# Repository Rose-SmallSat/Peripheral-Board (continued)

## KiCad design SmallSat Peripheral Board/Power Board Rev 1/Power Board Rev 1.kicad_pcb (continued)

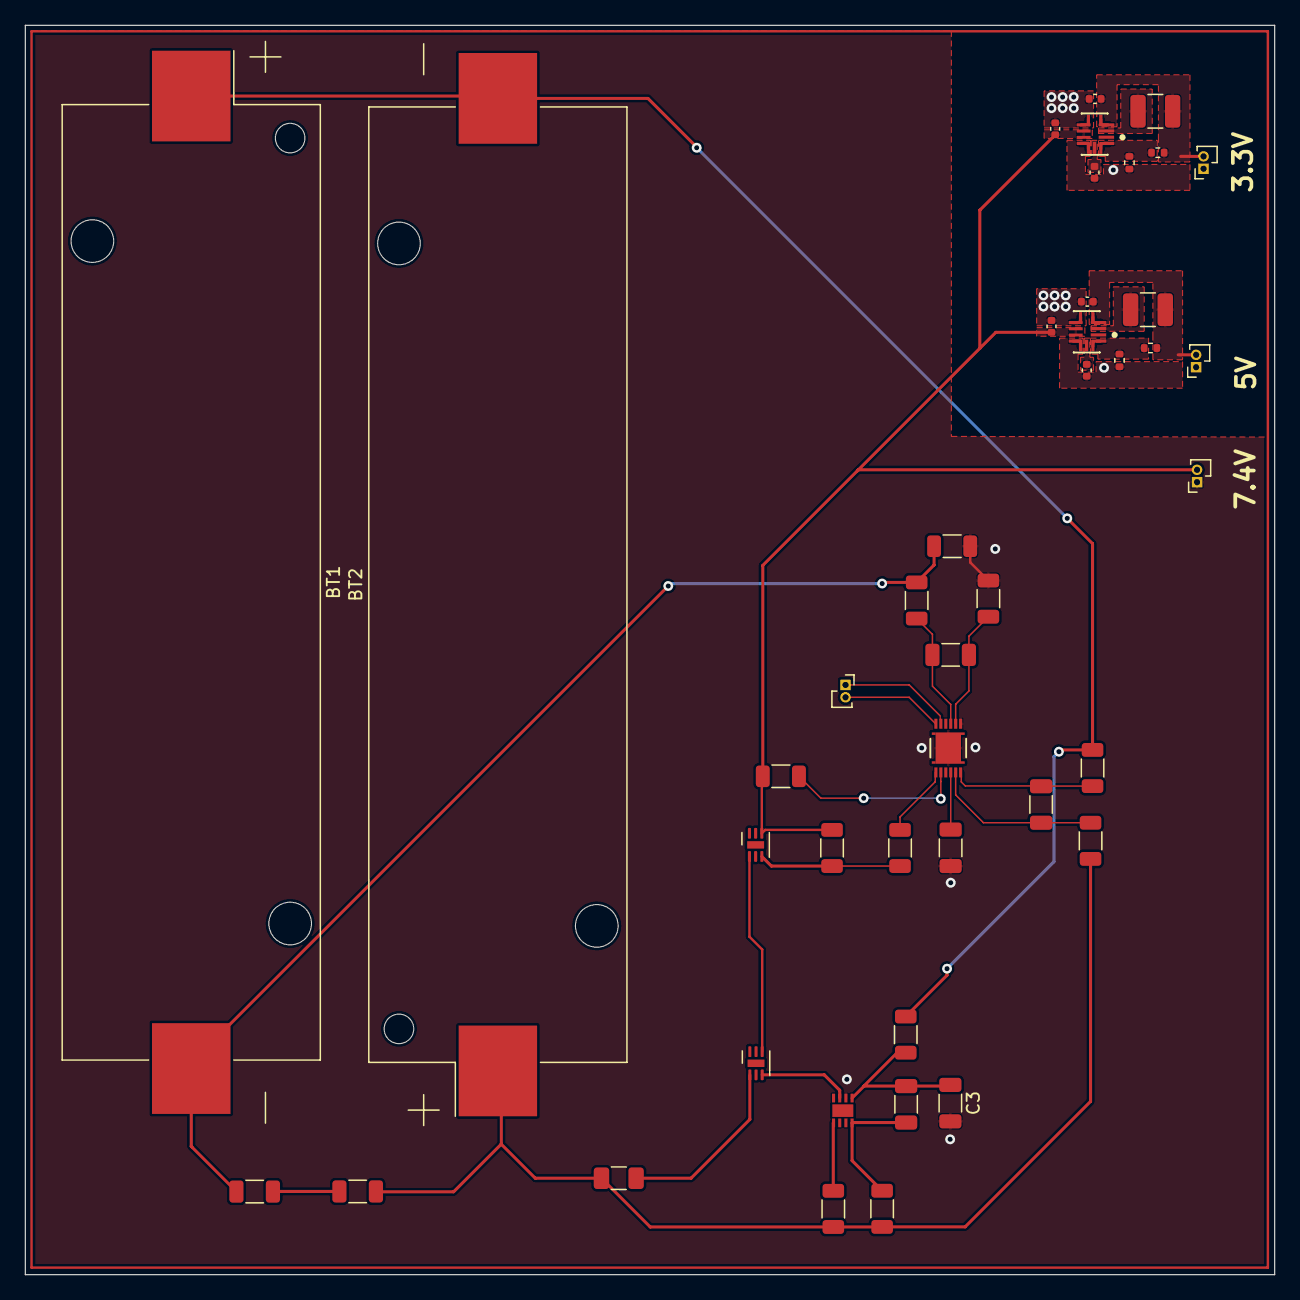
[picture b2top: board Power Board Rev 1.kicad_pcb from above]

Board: 2 copper layers, 101.1 x 101.1 mm, 43 parts (0 on the bottom side), 30 nets.

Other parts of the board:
J4: Conn_01x02_Pin; PinSocket_1x02_P1.00mm_Vertical

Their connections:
/Fuel_SCL: J4.1; also elsewhere on the board
/Fuel_SDA: J4.2; also elsewhere on the board

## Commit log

2024-01-27 added zip of Board
2024-01-27 add extracted board files
2024-02-02 Tim Commit :)
2024-02-04 Stepper Motor Materials
    Added this stuff for Steven to research wiuth
2024-02-04 A4988 datasheet added
2024-02-05 Schematic changes
2024-02-11 Updated Power Section
    Now using BQ28Z620DRZR fuel gauge
    Now using BQ296202DSGR protection
2024-02-18 Finished First Try for Power Board
2024-02-20 Started Power Board PCB
    - Schematic finished*
    - PCB started - starting to sort components
    - Need to get general layout done
2024-02-20 Power Board Grouping
    - Continuing to group parts
    - Connectors figured out
    - Filter circuit must be close to BQ298
2024-02-20 Current Line Outline Complete
    - OV/UV protection IC wired
    - fuel gauge not wired
2024-03-05 Power Board Connections Complete
2024-03-11 Power Board Rev 1 Gerber Files Generated
2024-03-26 PB-order version
    Sent the order in for Rev 1 power board with this version
2024-03-27 Peripheral Board Rev 1 Complete
    Time to test!
2024-04-10 ADCS Driver Work
    Nothing final yet
2024-04-12 ADCS Driver Rev 2
    - Redesigned the ESC with modern ICs that have bootstrapping infrastructure
2024-04-12 Organized Repository
    - Better overall file organization
    - Included necessary documentation to be filled out
    - Included KiCAD libraries
2024-04-21 Peripheral Board Progress
    - ADCS starting to be laid out
    - power board removed from peripheral board
